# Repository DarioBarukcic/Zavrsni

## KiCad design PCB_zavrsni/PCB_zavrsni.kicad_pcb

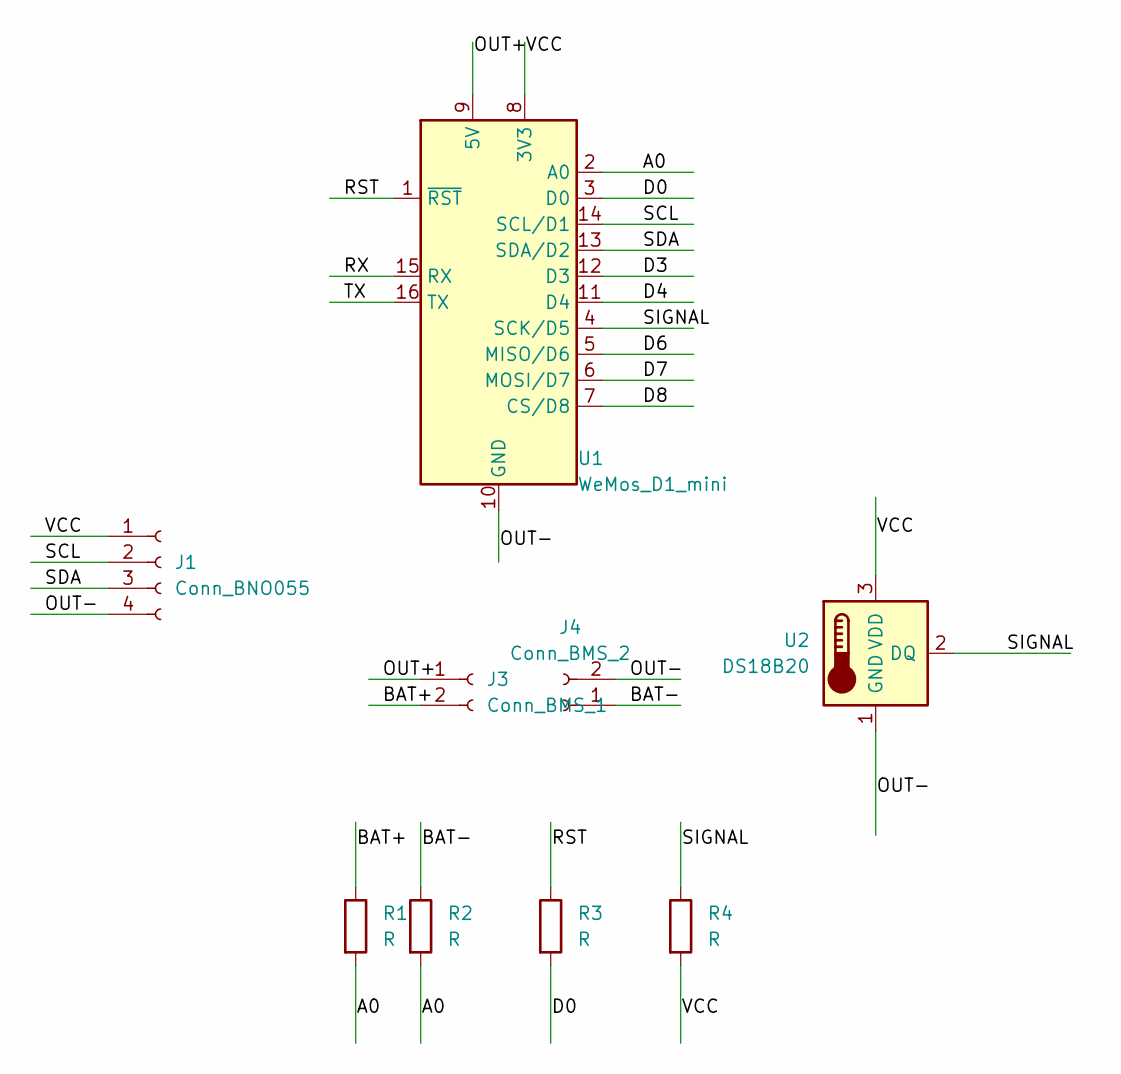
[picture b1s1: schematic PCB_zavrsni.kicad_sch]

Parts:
J1: Conn_BNO055; PinSocket_1x04_P2.54mm_Vertical
J3: Conn_BMS_1; PinSocket_1x02_P2.54mm_Vertical
J4: Conn_BMS_2; PinSocket_1x02_P2.54mm_Vertical
R1, R2, R3, R4: R; R_Axial_DIN0204_L3.6mm_D1.6mm_P7.62mm_Horizontal
U1: WeMos_D1_mini; WEMOS_D1_mini_light
U2: DS18B20; TO-92_Inline

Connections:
/A0: R1.2, R2.2, U1.2 (A0)
/BAT+: J3.2, R1.1
/BAT-: J4.1, R2.1
/D0: R3.2, U1.3 (D0)
/D3: U1.12 (D3)
/D4: U1.11 (D4)
/D6: U1.5 (MISO/D6)
/D7: U1.6 (MOSI/D7)
/D8: U1.7 (CS/D8)
/OUT+: J3.1, U1.9 (5V)
/OUT-: J1.4, J4.2, U1.10 (GND), U2.1 (GND)
/RST: R3.1, U1.1 (~RST)
/RX: U1.15 (RX)
/SCL: J1.2, U1.14 (SCL/D1)
/SDA: J1.3, U1.13 (SDA/D2)
/SIGNAL: R4.1, U1.4 (SCK/D5), U2.2 (DQ)
/TX: U1.16 (TX)
/VCC: J1.1, R4.2, U1.8 (3V3), U2.3 (VDD)

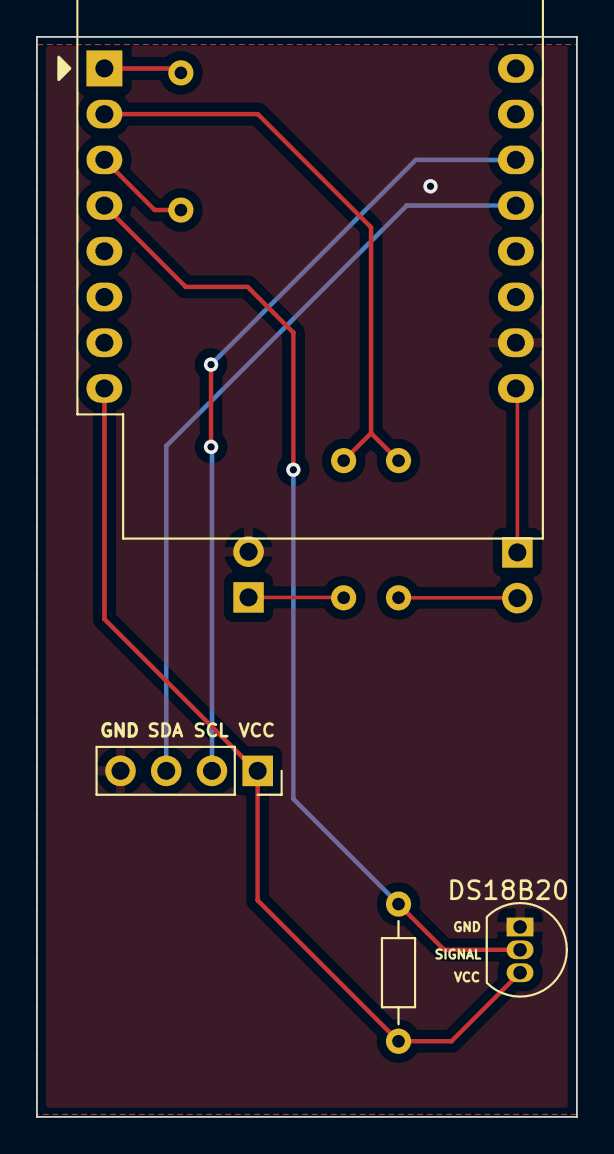
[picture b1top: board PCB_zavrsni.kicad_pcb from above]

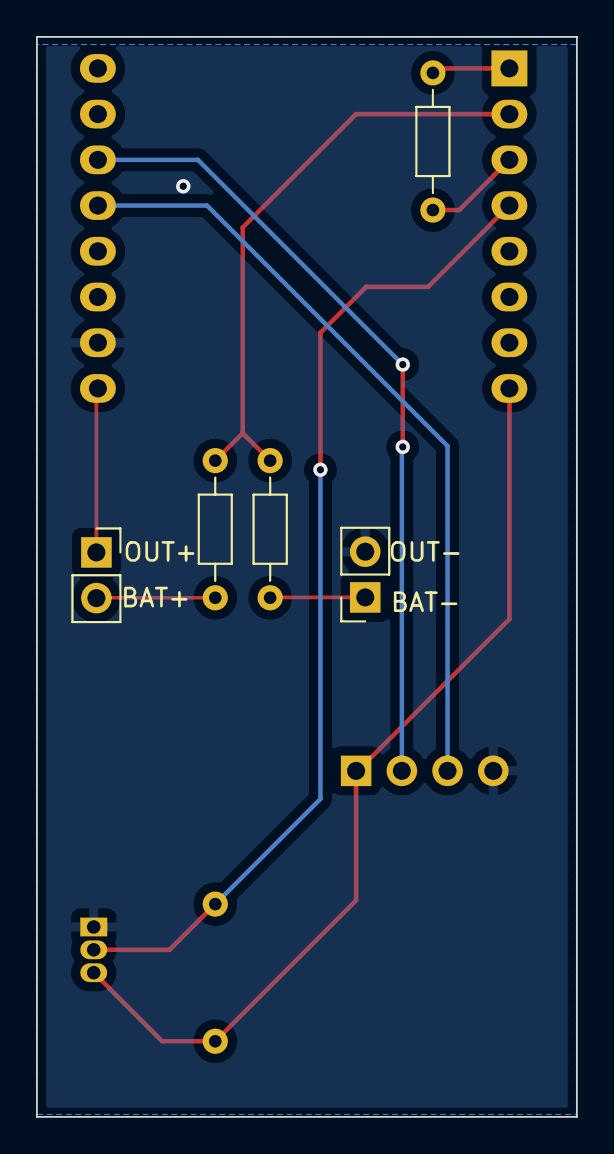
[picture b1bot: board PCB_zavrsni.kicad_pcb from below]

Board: 2 copper layers, 30.0 x 60.0 mm, 9 parts (5 on the bottom side), 11 nets.
